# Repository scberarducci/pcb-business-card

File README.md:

# PCB Business Card
Design for Altium Academy's PCB Business Card Design Challenge (2026). Original design by Sara Berarducci. 
Open Hardware for educational use.

## License
*The hardware design files in this repository are licensed under the CERN Open Hardware Licence Version 2 - Weakly Reciprocal (CERN-OHL-W-2.0).*
*See LICENSE.txt for the full license text.*
*Educational use is encouraged, including use in classrooms and workshops.*
*Name, logo, and personal branding are **not** licensed for reuse except for attribution/reference purposes.*

## Description

This PCB business card is a functional 7-stage transistor loop oscillator visualized with LEDs. The loop oscillator is powered while a pushbutton is held and otherwise remains off.

The design includes startup asymmetry at the first stage using a capacitor and diode, which helps ensure consistent startup and quick reset when power is removed.

The included BOM contains all parts used in the original fabricated card, rev 1.0, except the coin cell holder, which is a Keystone 3000 CR1220 clip.

## Build Notes

The card was designed with JLCPCB's manufacturing capabilities in mind. It is powered by a CR1220 coin cell battery.

Voltage sag during extended use is expected. If the circuit is powered for long stretches of time, oscillation may slow and the LEDs may dim.

Rev 2.0 is currently in progress and will be added to this repository once completed. See the demos folder for images and videos of the fabricated card.

If you use this design to create a PCB of your own, I would love to see it! Feel free to email me at scberarducci@gmail.com or contact me on LinkedIn with your design.

## Repository Contents
* hardware/ — KiCad hardware design files and BOM
* demos/ — images and videos of the fabricated card
* logo/ — logo/reference assets used in the design - *not licensed for use other than for attribution purposes*

## Attribution
When using or sharing this design, attribution is requested.
**Sara Berarducci**
https://www.saraberarducci.com/hardware/altium-business-card-challenge

## Copyright
**Copyright (c) 2026 Sara Berarducci**

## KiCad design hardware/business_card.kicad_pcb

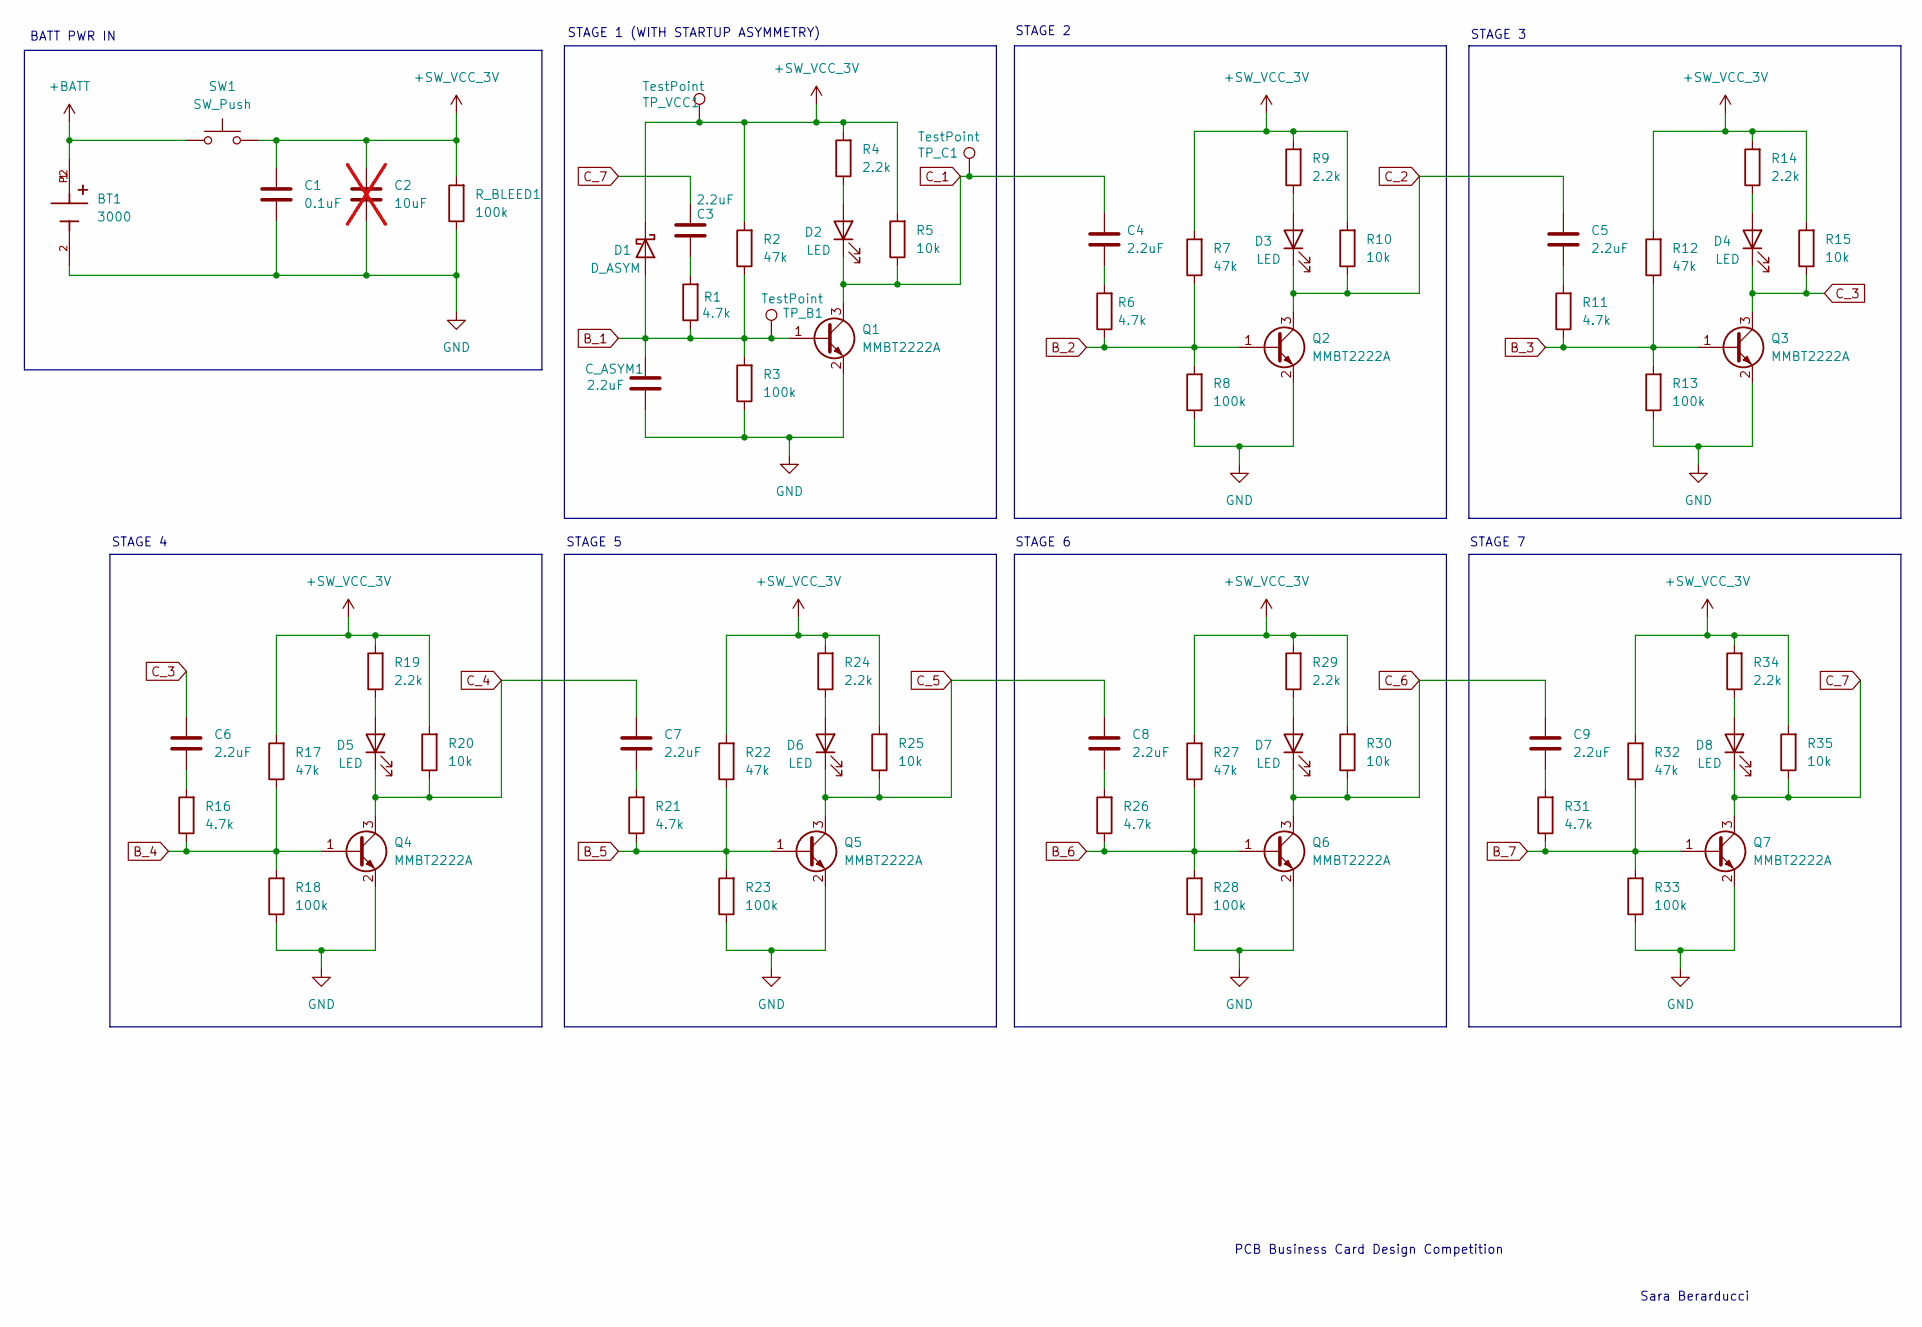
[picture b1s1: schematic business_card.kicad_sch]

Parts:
BT1: 3000; BatteryHolder_Keystone_3000_1x12mm; PARTREV M
C1: 0.1uF; C_0603_1608Metric_Pad1.08x0.95mm_HandSolder
C2: 10uF; C_0603_1608Metric_Pad1.08x0.95mm_HandSolder; not fitted
C3, C4, C5, C6, C7, C8, C9: 2.2uF; C_0805_2012Metric_Pad1.18x1.45mm_HandSolder
C_ASYM1: 2.2uF; C_0805_2012Metric_Pad1.18x1.45mm_HandSolder
D1: D_ASYM; D_0603_1608Metric_Pad1.05x0.95mm_HandSolder
D2, D3, D4, D5, D6, D7, D8: LED; LED_0805_2012Metric_Pad1.15x1.40mm_HandSolder
Q1, Q2, Q3, Q4, Q5, Q6, Q7: MMBT2222A; SOT-23
R1, R6, R11, R16, R21, R26, R31: 4.7k; R_0603_1608Metric_Pad0.98x0.95mm_HandSolder
R2, R7, R12, R17, R22, R27, R32: 47k; R_0603_1608Metric_Pad0.98x0.95mm_HandSolder
R3, R8, R13, R18, R23, R28, R33: 100k; R_0603_1608Metric_Pad0.98x0.95mm_HandSolder
R4, R9, R14, R19, R24, R29, R34: 2.2k; R_0603_1608Metric_Pad0.98x0.95mm_HandSolder
R5, R10, R15, R20, R25, R30, R35: 10k; R_0603_1608Metric_Pad0.98x0.95mm_HandSolder
R_BLEED1: 100k; R_0603_1608Metric_Pad0.98x0.95mm_HandSolder
SW1: SW_Push; SW_SPST_CK_RS282G05A3
TP_B1: TestPoint; TestPoint_Pad_D1.5mm
TP_C1: TestPoint; TestPoint_Pad_D1.5mm
TP_VCC1: TestPoint; TestPoint_Pad_D1.5mm

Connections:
+BATT: BT1.1, BT1.P2, SW1.1
+SW_VCC_3V: C1.1, C2.1, D1.1 (K), R2.2, R4.2, R5.2, R7.2, R9.2, R10.2, R12.2, R14.2, R15.2, R17.2, R19.2, R20.2, R22.2, R24.2, R25.2, R27.2, R29.2, R30.2, R32.2, R34.2, R35.2, R_BLEED1.2, SW1.2, TP_VCC1.1
B_1: C_ASYM1.2, D1.2 (A), Q1.1 (B), R1.1, R2.1, R3.2, TP_B1.1
B_2: Q2.1 (B), R6.1, R7.1, R8.2
B_3: Q3.1 (B), R11.1, R12.1, R13.2
B_4: Q4.1 (B), R16.1, R17.1, R18.2
B_5: Q5.1 (B), R21.1, R22.1, R23.2
B_6: Q6.1 (B), R26.1, R27.1, R28.2
B_7: Q7.1 (B), R31.1, R32.1, R33.2
C_1: C4.1, D2.1 (K), Q1.3 (C), R5.1, TP_C1.1
C_2: C5.1, D3.1 (K), Q2.3 (C), R10.1
C_3: C6.1, D4.1 (K), Q3.3 (C), R15.1
C_4: C7.1, D5.1 (K), Q4.3 (C), R20.1
C_5: C8.1, D6.1 (K), Q5.3 (C), R25.1
C_6: C9.1, D7.1 (K), Q6.3 (C), R30.1
C_7: C3.1, D8.1 (K), Q7.3 (C), R35.1
GND: BT1.2, C1.2, C2.2, C_ASYM1.1, Q1.2 (E), Q2.2 (E), Q3.2 (E), Q4.2 (E), Q5.2 (E), Q6.2 (E), Q7.2 (E), R3.1, R8.1, R13.1, R18.1, R23.1, R28.1, R33.1, R_BLEED1.1
unnamed: C3.2, R1.2
unnamed: C4.2, R6.2
unnamed: C5.2, R11.2
unnamed: C6.2, R16.2
unnamed: C7.2, R21.2
unnamed: C8.2, R26.2
unnamed: C9.2, R31.2
unnamed: D2.2 (A), R4.1
unnamed: D3.2 (A), R9.1
unnamed: D4.2 (A), R14.1
unnamed: D5.2 (A), R19.1
unnamed: D6.2 (A), R24.1
unnamed: D7.2 (A), R29.1
unnamed: D8.2 (A), R34.1

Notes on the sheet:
STAGE 3
STAGE 2
PCB Business Card Design Competition
STAGE 4
Sara Berarducci
STAGE 6
STAGE 1 (WITH STARTUP ASYMMETRY)
STAGE 5
STAGE 7
BATT PWR IN

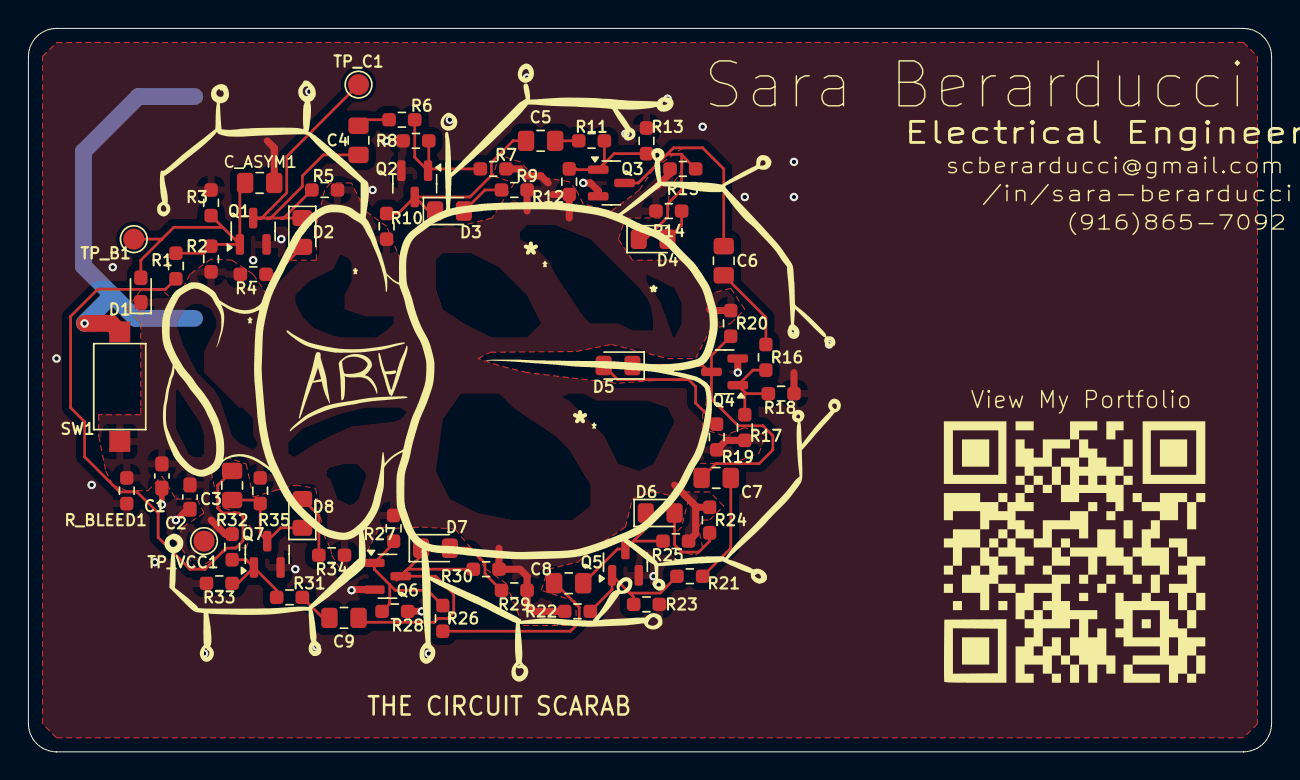
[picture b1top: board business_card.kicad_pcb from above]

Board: 2 copper layers, 88.5 x 51.5 mm, 66 parts (1 on the bottom side), 31 nets.

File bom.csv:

Designator,Footprint,Quantity,Value,LCSC Part #
BT1,BatteryHolder_Keystone_3000_1x12mm,1,3000,
C1,0603,1,0.1uF,
C2,0603,1,10uF,
"C3, C4, C5, C6, C7, C8, C9, C_ASYM1",0805,8,2.2uF,
D1,0603,1,D_ASYM,
"D2, D3, D4, D5, D6, D7, D8",0805,7,LED,
"Q1, Q2, Q3, Q4, Q5, Q6, Q7",SOT-23,7,MMBT2222A,
"R1, R11, R16, R21, R26, R31, R6",0603,7,4.7k,
"R10, R15, R20, R25, R30, R35, R5",0603,7,10k,
"R12, R17, R2, R22, R27, R32, R7",0603,7,47k,
"R13, R18, R23, R28, R3, R33, R8, R_BLEED1",0603,8,100k,
"R14, R19, R24, R29, R34, R4, R9",0603,7,2.2k,
SW1,SW_SPST_CK_RS282G05A3,1,SW_Push,
"TP_B1, TP_C1, TP_VCC1",TestPoint_Pad_D1.5mm,3,TestPoint,
